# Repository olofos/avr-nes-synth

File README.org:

* NESSynth

  /NESSynth/ is an overcomplicated machine that plays NES music. /NESSynth/ currently supports four of the five channels present in the NES Audio Processing Unit (APU):
  - Two pulse, or square wave, channels
  - A triangle wave
  - A random noise channel

  There is currently no support for a DCM channel.

  /NESSynth/ has a menu system where the user can choose which game soundtrack is to be played.
  There is furthermore support for a playlist to which individual tracks can be added and played back.

** Hardware overview

  Each *channel* is processed separately by firmware running on an 8-bit ATMega88p microcontroller.
  An ATMega328p microcontroller acts as a central *controller*, reading track information from an SD card and writing the corresponding instructions to the channels.
  The controller is furthermore connected to an 128x64 pixel SSD1306 OLED display on which information about the current track, as well as a simple menu system, is displayed.
  User input is processed through an additional ATMega88p microcontroller which acts like an *io-bridge*, communicating with the main controller over I2C.
  The io-bridge is connected to four user buttons, four LEDs an a UART header for debugging.

  The following block diagram gives an overview of the architecture of /NESSynth/.

  #+HTML: 

*** 8-bit bus

   The controller communicates with the channels using an *8-bit parallel bus*.
   Writes to the bus are signalled on the *data clock* line.
   A rising clock signals that an address has been written on the bus, and a falling clock signals that a value that is to be written to the register at the previous address has been written on the bus.
   A new address or value is written every 33us, and the channels have to ensure that the data has been read from the bus within that time frame.

*** Frame clock

   In addition to the 8-bit bus, the controller provides the channel with a frame clock, which fires at a constant rate of 240 Hz.
   The frame clock is used to regularly update the output wave forms by applying the various effects such as the length counters and sweep units.

*** Channels

   Each channel emulates one of the channels on the NES APU.
   They react to writes to the corresponding registers appearing on the data bus and at each tick of the frame clock they clock the relevant output units in order to create effects such as sweep and envelope decay.

   The channels output sound at a frequency that is obtained by dividing the NTSC APU frequency of 1.789773 MHz by an integer, the /period/.
   The microcontrollers in the channels are clocked using a crystal with resonant frequency 14.3818 MHz, which is a multiple of the APU frequency.

   The PCBs of the channels have two jumpers, *CONF0* and *CONF1*, which can be used to configure which of the four APU channels the microcontroller is emulating.
   The possible settings are given in the following table.

   | CONF1      | CONF0      | Channel        |
   |------------+------------+----------------|
   | Fitted     | Fitted     | Square wave #1 |
   | Fitted     | Not fitted | Square wave #2 |
   | Not fitted | Fitted     | Triangle wave  |
   | Not fitted | Not fitted | Noise          |

   Each channel has a four bit R2R DAC that is used to construct the outgoing audio wave form.

   - Square wave channels

     The two square wave channels output a square wave with a duty cycle that can be set to 12.5%, 25%, 50% or 75%. The output volume of the square wave channels can be set to one of 16 levels, and can be modulated using the envelope decay unit. The square wave channels further support a sweep function to modulate the output frequency, as well as a length counter.

   - Triangle wave

     The triangle wave channel outputs a 32-step triangle wave of constant volume. For a given period, the frequency of the triangle wave is half of that of a square wave of the same period. The triangle wave channel supports a length counter and a linear counter which both can be used to limit the amount of time a note is played.

   - Noise channel

     The noise channel outputs noise that is generated using a linear feedback shift register. The feedback can be taken from two different taps of the shift registers. The volume of the noise channel can be configured to be constant, with 16 possible output levels, or can be varied over time using the envelope decay unit. The noise channel also supports a length counter.

*** Audio output

    The output of each channel is mixed together and then passed through a low pass filter with corner frequency 16 Hz and a high pass filter with corner frequency 16 kHz.
    The signal is the amplified using an LM386 audio amplifier before going to an 8 ohm speaker.

** Firmware

   The firmware for /NESSynth/ consists of three main pieces: the firmware for the main controller, the io-bridge and for the channels.
   The firmware is written using [[http://www.nongnu.org/avr-libc/user-manual/][avr-libc]] and compiled using avr-gcc.

   The controller has a menu system which is displayed on the OLED display.
   The menu system supports menus stored either on an SD card, in the flash memory of the controller, or in the EEPROM.
   It allows the user to play all the tracks from a particular game or to create a playlist with up to 128 tracks.
   The playlist is stored in the EEPROM of the controller.

   When playing a track, the controller reads the song data from the SD card where it is stored in a custom binary format (see below).
   The song data records the state of the APU registers at 60 Hz, and the controller outputs the data on the 8-bit bus.
   The song data is split into frames, and the controller plays the frames back at 60 Hz.

   The controller firmware includes a custom SD card and FAT32 drivers.
   The FAT32 driver does not read the FAT table into memory, which means that it has to search the table while reading data off the SD card.
   To improve performance when seeking in small files there is a cluster cache where the first few clusters in the currently open file.

   The firmware of the channels simply listens to writes to the registers relevant to the corresponding APU channel and puts out a wave form on the DAC.
   The channel firmware is heavily interrupt based.
   In order to improve the performance of the main timer interrupt, which is responsible for actually constructing the audio out signal, the interrupt handler has been written in assembly code.
   For clarity there is also a C version of the interrupt handler, which can be enabled by removing the ASMINTERRUPT flag in the Makefile of the channel firmware source code.

*** Song file format

   The binary file format is very simple.
   It consists of a number of two-byte records, with the first byte indicating an address, and the second byte the corresponding values.
   There are three special records

   | Address | Value | Meaning      |
   |---------+-------+--------------|
   |    0xF1 |  0xF1 | End of frame |
   |    0xFF |  0xFF | End of file  |
   |    0xFE |  0xFE | Loop         |

   The loop record is followed by a 16-bit byte address indicating which byte in the file to loop back to.

   In order to construct a data file from an NSF files, a player based on a custom version of the [[http://www.slack.net/~ant/libs/audio.html#Game_Music_Emu][Game_Music_Emu 0.5.2]] library is used.
   The custom NSF player outputs data in a text file.
   This data is then processed through a couple of simple programs which are used to detect loops in the track, and to convert the data into the binary file format described above.

** Acknowledgements

   The [[https://wiki.nesdev.com/w/index.php/APU][APU pages]] of the [[https://wiki.nesdev.com/][NesDev wiki]] have been invaluable for providing information about the inner workings of the NES APU, as has the [[http://nesdev.com/NESSOUND.txt][NESSOUND]] document by Brad Taylor.

   The NSF player that is used to create binary sound data files is based on the  [[http://www.slack.net/~ant/libs/audio.html#Game_Music_Emu][Game_Music_Emu 0.5.2]] library by Shay Green, which is licensed under the [[https://www.gnu.org/licenses/old-licenses/lgpl-2.1.en.html][GNU Lesser General Public License, Version 2.1]].

   The circular buffer implementation in lib/cbuf.h is inspired by the one in [[https://github.com/dhylands/TimerUART][TimerUART]].

   For 3d rendering of the boards, 3d models from [[https://github.com/ab2tech/KiCad][ab2tech]], which are licensed under [[http://creativecommons.org/licenses/by-nc-sa/3.0/deed.en_US][Creative Commons Attribution-NonCommercial-ShareAlike 3.0 Unported License]], and from [[https://github.com/JorgeAparicio/libKiCad][libKiCad]], which are licensed under [[hardware/lib/3d_models/walter/license.txt][Creative Commons license v3.0, Attribution-Share Alike]], have been used.

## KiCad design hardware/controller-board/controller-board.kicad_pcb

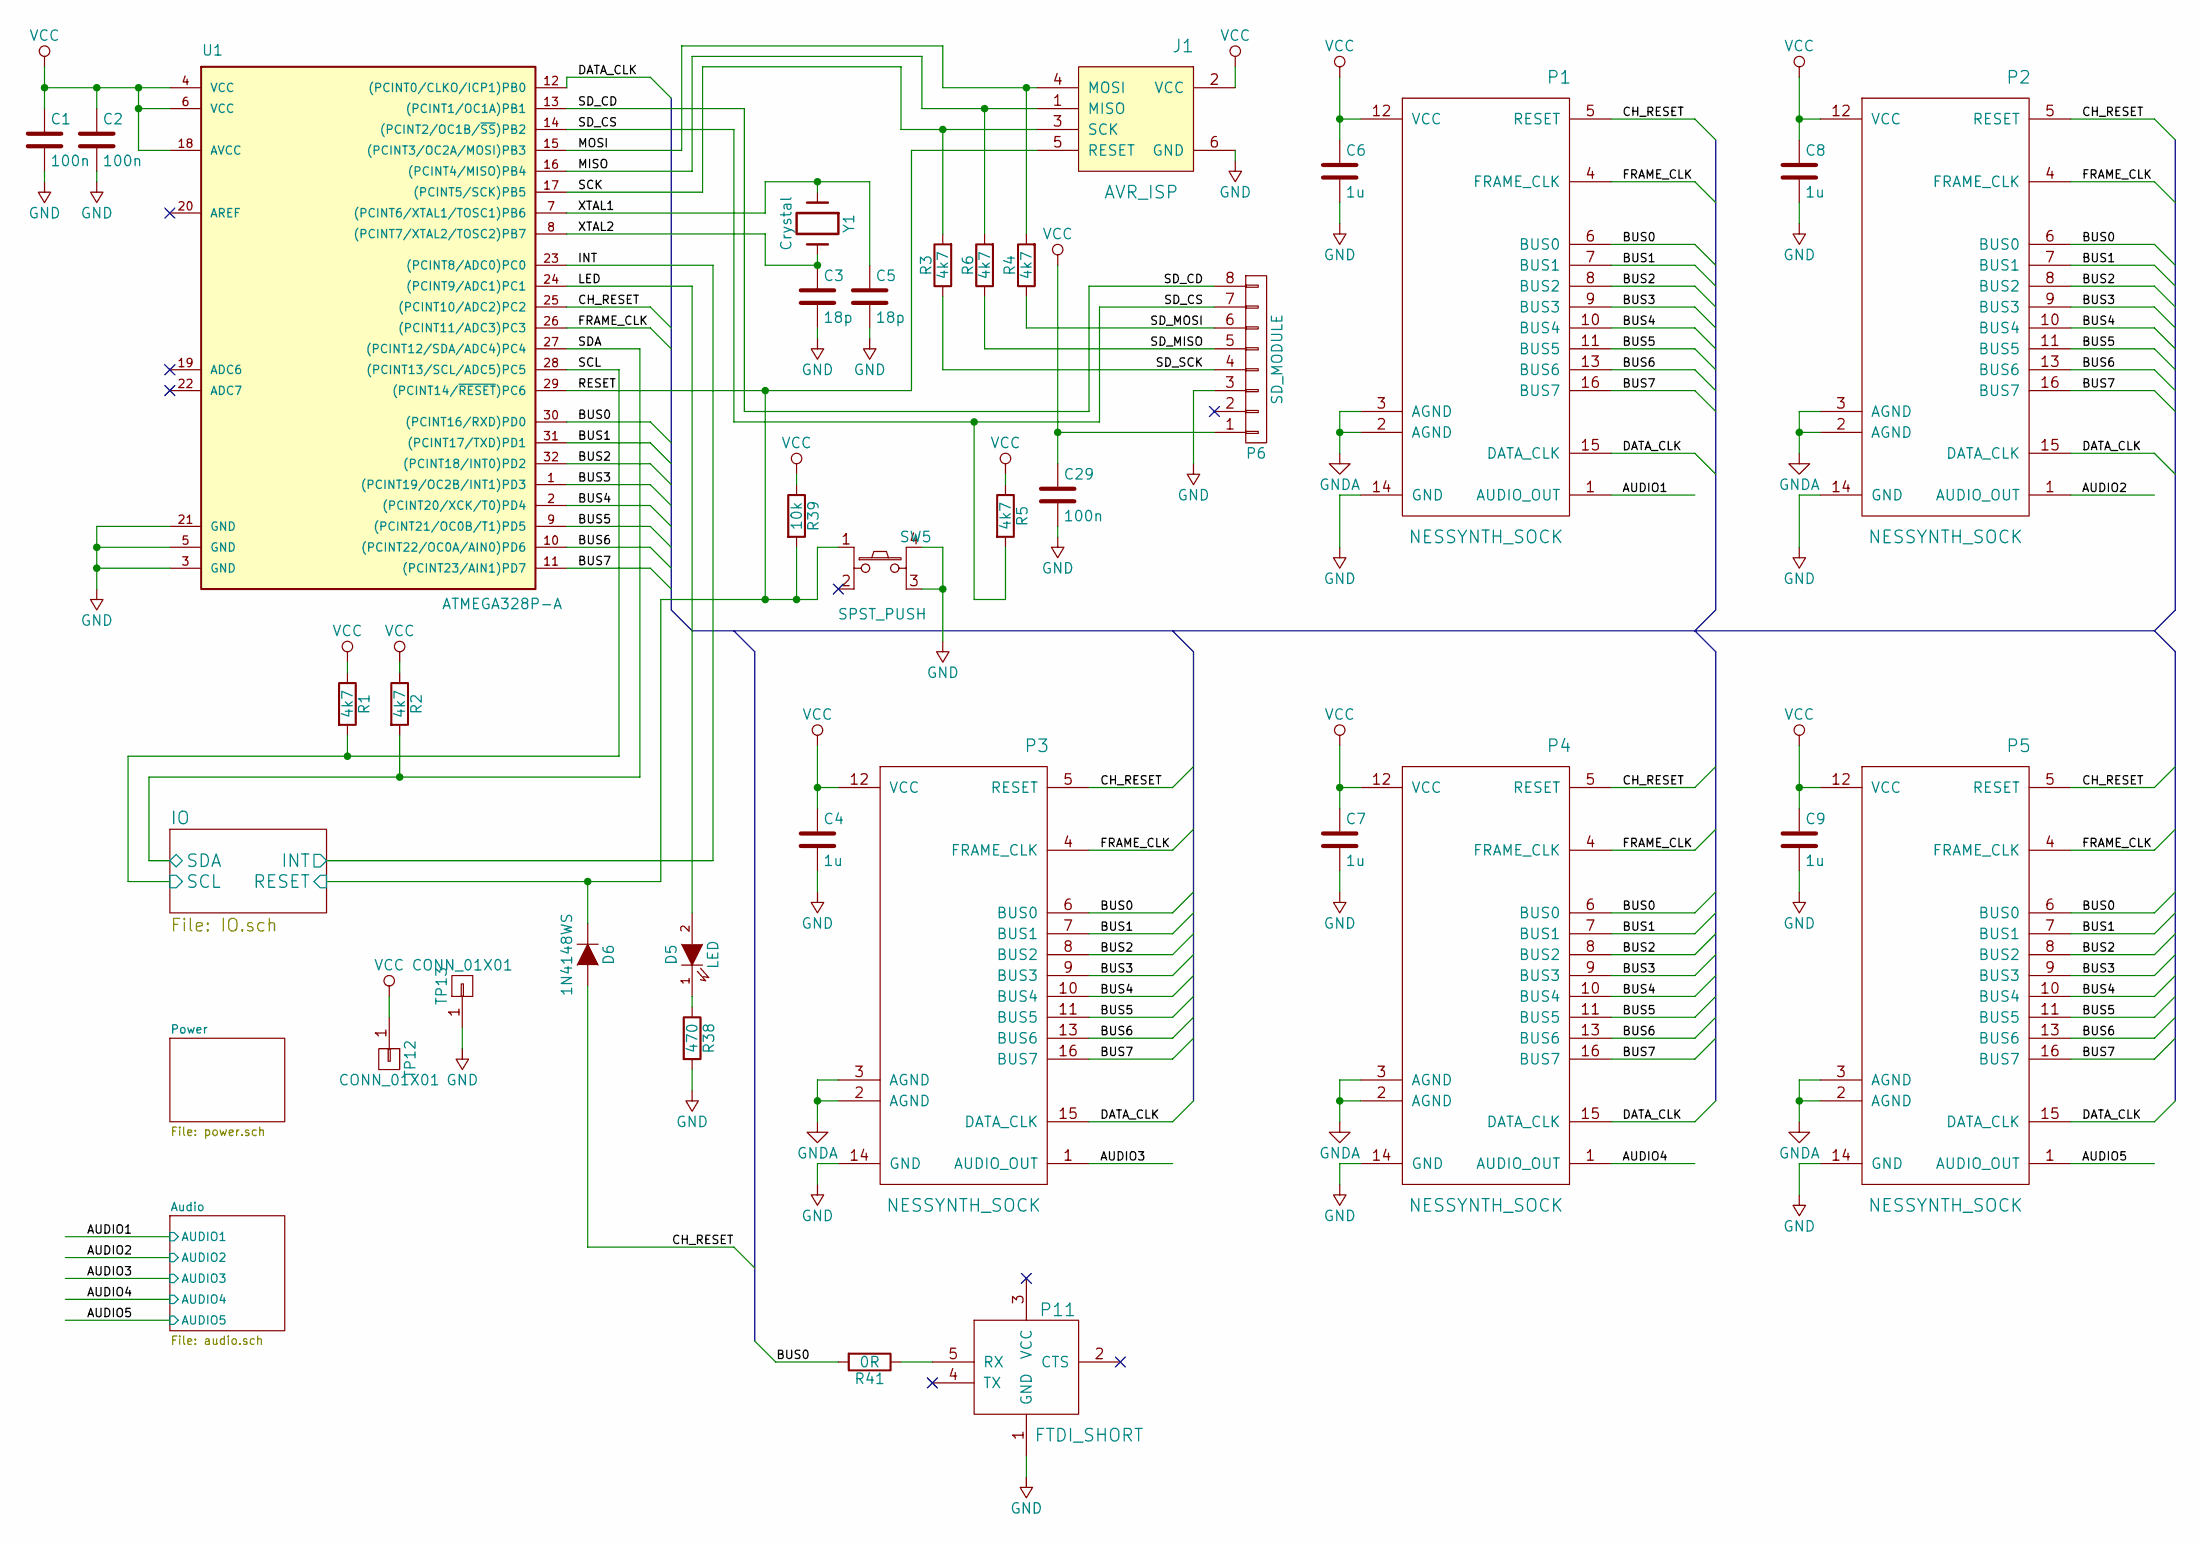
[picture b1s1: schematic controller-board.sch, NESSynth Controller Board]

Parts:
C1, C2, C29: 100n; C_0805_HandSoldering
C3, C5: 18p; C_0805_HandSoldering
C4, C6, C7, C8, C9: 1u; C_0805_HandSoldering
D5: LED; LED_0805
D6: 1N4148WS; SOD-323
J1: AVR_ISP; AVR_ISP_SMALL
P1, P2, P3, P4, P5: NESSYNTH_SOCK; Socket_Strip_Straight_2x08
P6: SD_MODULE; Socket_Strip_Straight_1x08
P11: FTDI_SHORT; Pin_Header_Straight_1x05
R1, R2, R3, R4, R5, R6: 4k7; R_0805_HandSoldering
R38: 470; R_0805_HandSoldering
R39: 10k; R_0805_HandSoldering
R41: 0R; R_0805_HandSoldering
SW5: SPST_PUSH; SW_PUSH_SMALL_4
TP12: CONN_01X01; Measurement_Point_Round-SMD-Pad_Small
TP13: CONN_01X01; Measurement_Point_Square-SMD-Pad_Small
U1: ATMEGA328P-A; TQFP-32_7x7mm_Pitch0.8mm
Y1: Crystal; Crystal_HC49-U_Vertical

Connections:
/Audio/AUDIO1: P1.1 (AUDIO_OUT); also elsewhere on the board
/Audio/AUDIO2: P2.1 (AUDIO_OUT); also elsewhere on the board
/Audio/AUDIO3: P3.1 (AUDIO_OUT); also elsewhere on the board
/Audio/AUDIO4: P4.1 (AUDIO_OUT); also elsewhere on the board
/Audio/AUDIO5: P5.1 (AUDIO_OUT); also elsewhere on the board
/BUS0: P1.6 (BUS0), P2.6 (BUS0), P3.6 (BUS0), P4.6 (BUS0), P5.6 (BUS0), R41.2, U1.30 ((PCINT16/RXD)PD0)
/BUS1: P1.7 (BUS1), P2.7 (BUS1), P3.7 (BUS1), P4.7 (BUS1), P5.7 (BUS1), U1.31 ((PCINT17/TXD)PD1)
/BUS2: P1.8 (BUS2), P2.8 (BUS2), P3.8 (BUS2), P4.8 (BUS2), P5.8 (BUS2), U1.32 ((PCINT18/INT0)PD2)
/BUS3: P1.9 (BUS3), P2.9 (BUS3), P3.9 (BUS3), P4.9 (BUS3), P5.9 (BUS3), U1.1 ((PCINT19/OC2B/INT1)PD3)
/BUS4: P1.10 (BUS4), P2.10 (BUS4), P3.10 (BUS4), P4.10 (BUS4), P5.10 (BUS4), U1.2 ((PCINT20/XCK/T0)PD4)
/BUS5: P1.11 (BUS5), P2.11 (BUS5), P3.11 (BUS5), P4.11 (BUS5), P5.11 (BUS5), U1.9 ((PCINT21/OC0B/T1)PD5)
/BUS6: P1.13 (BUS6), P2.13 (BUS6), P3.13 (BUS6), P4.13 (BUS6), P5.13 (BUS6), U1.10 ((PCINT22/OC0A/AIN0)PD6)
/BUS7: P1.16 (BUS7), P2.16 (BUS7), P3.16 (BUS7), P4.16 (BUS7), P5.16 (BUS7), U1.11 ((PCINT23/AIN1)PD7)
/CH_RESET: D6.2 (A), P1.5 (RESET), P2.5 (RESET), P3.5 (RESET), P4.5 (RESET), P5.5 (RESET), U1.25 ((PCINT10/ADC2)PC2)
/DATA_CLK: P1.15 (DATA_CLK), P2.15 (DATA_CLK), P3.15 (DATA_CLK), P4.15 (DATA_CLK), P5.15 (DATA_CLK), U1.12 ((PCINT0/CLKO/ICP1)PB0)
/FRAME_CLK: P1.4 (FRAME_CLK), P2.4 (FRAME_CLK), P3.4 (FRAME_CLK), P4.4 (FRAME_CLK), P5.4 (FRAME_CLK), U1.26 ((PCINT11/ADC3)PC3)
/IO/INT: U1.23 ((PCINT8/ADC0)PC0); also elsewhere on the board
/IO/RESET: D6.1 (K), J1.5 (RESET), R39.2, SW5.1 (A1), U1.29 ((PCINT14/~RESET~)PC6); also elsewhere on the board
/IO/SCL: R1.2, U1.28 ((PCINT13/SCL/ADC5)PC5); also elsewhere on the board
/IO/SDA: R2.2, U1.27 ((PCINT12/SDA/ADC4)PC4); also elsewhere on the board
/LED: D5.2 (A), U1.24 ((PCINT9/ADC1)PC1)
/MISO: J1.1 (MISO), R6.2, U1.16 ((PCINT4/MISO)PB4)
/MOSI: J1.4 (MOSI), R4.2, U1.15 ((PCINT3/OC2A/MOSI)PB3)
/SCK: J1.3 (SCK), R3.2, U1.17 ((PCINT5/SCK)PB5)
/SD_CD: P6.8, U1.13 ((PCINT1/OC1A)PB1)
/SD_CS: P6.7, R5.2, U1.14 ((PCINT2/OC1B/~SS~)PB2)
/SD_MISO: P6.5, R6.1
/SD_MOSI: P6.6, R4.1
/SD_SCK: P6.4, R3.1
/XTAL1: C5.1, U1.7 ((PCINT6/XTAL1/TOSC1)PB6), Y1.1
/XTAL2: C3.1, U1.8 ((PCINT7/XTAL2/TOSC2)PB7), Y1.2
GND: C1.2, C2.2, C3.2, C4.2, C5.2, C6.2, C7.2, C8.2, C9.2, C29.2, J1.6 (GND), P1.2 (AGND), P1.3 (AGND), P1.14 (GND), P2.2 (AGND), P2.3 (AGND), P2.14 (GND), P3.2 (AGND), P3.3 (AGND), P3.14 (GND), P4.2 (AGND), P4.3 (AGND), P4.14 (GND), P5.2 (AGND), P5.3 (AGND), P5.14 (GND), P6.3, P11.1 (GND), R38.2, SW5.3 (B2), SW5.4 (B1), TP13.1, U1.3 (GND), U1.5 (GND), U1.21 (GND); also elsewhere on the board
unnamed: D5.1 (K), R38.1
unnamed: P11.5 (RX), R41.1
VCC: C1.1, C2.1, C4.1, C6.1, C7.1, C8.1, C9.1, C29.1, J1.2 (VCC), P1.12 (VCC), P2.12 (VCC), P3.12 (VCC), P4.12 (VCC), P5.12 (VCC), P6.1, R1.1, R2.1, R5.1, R39.1, TP12.1, U1.4 (VCC), U1.6 (VCC), U1.18 (AVCC); also elsewhere on the board

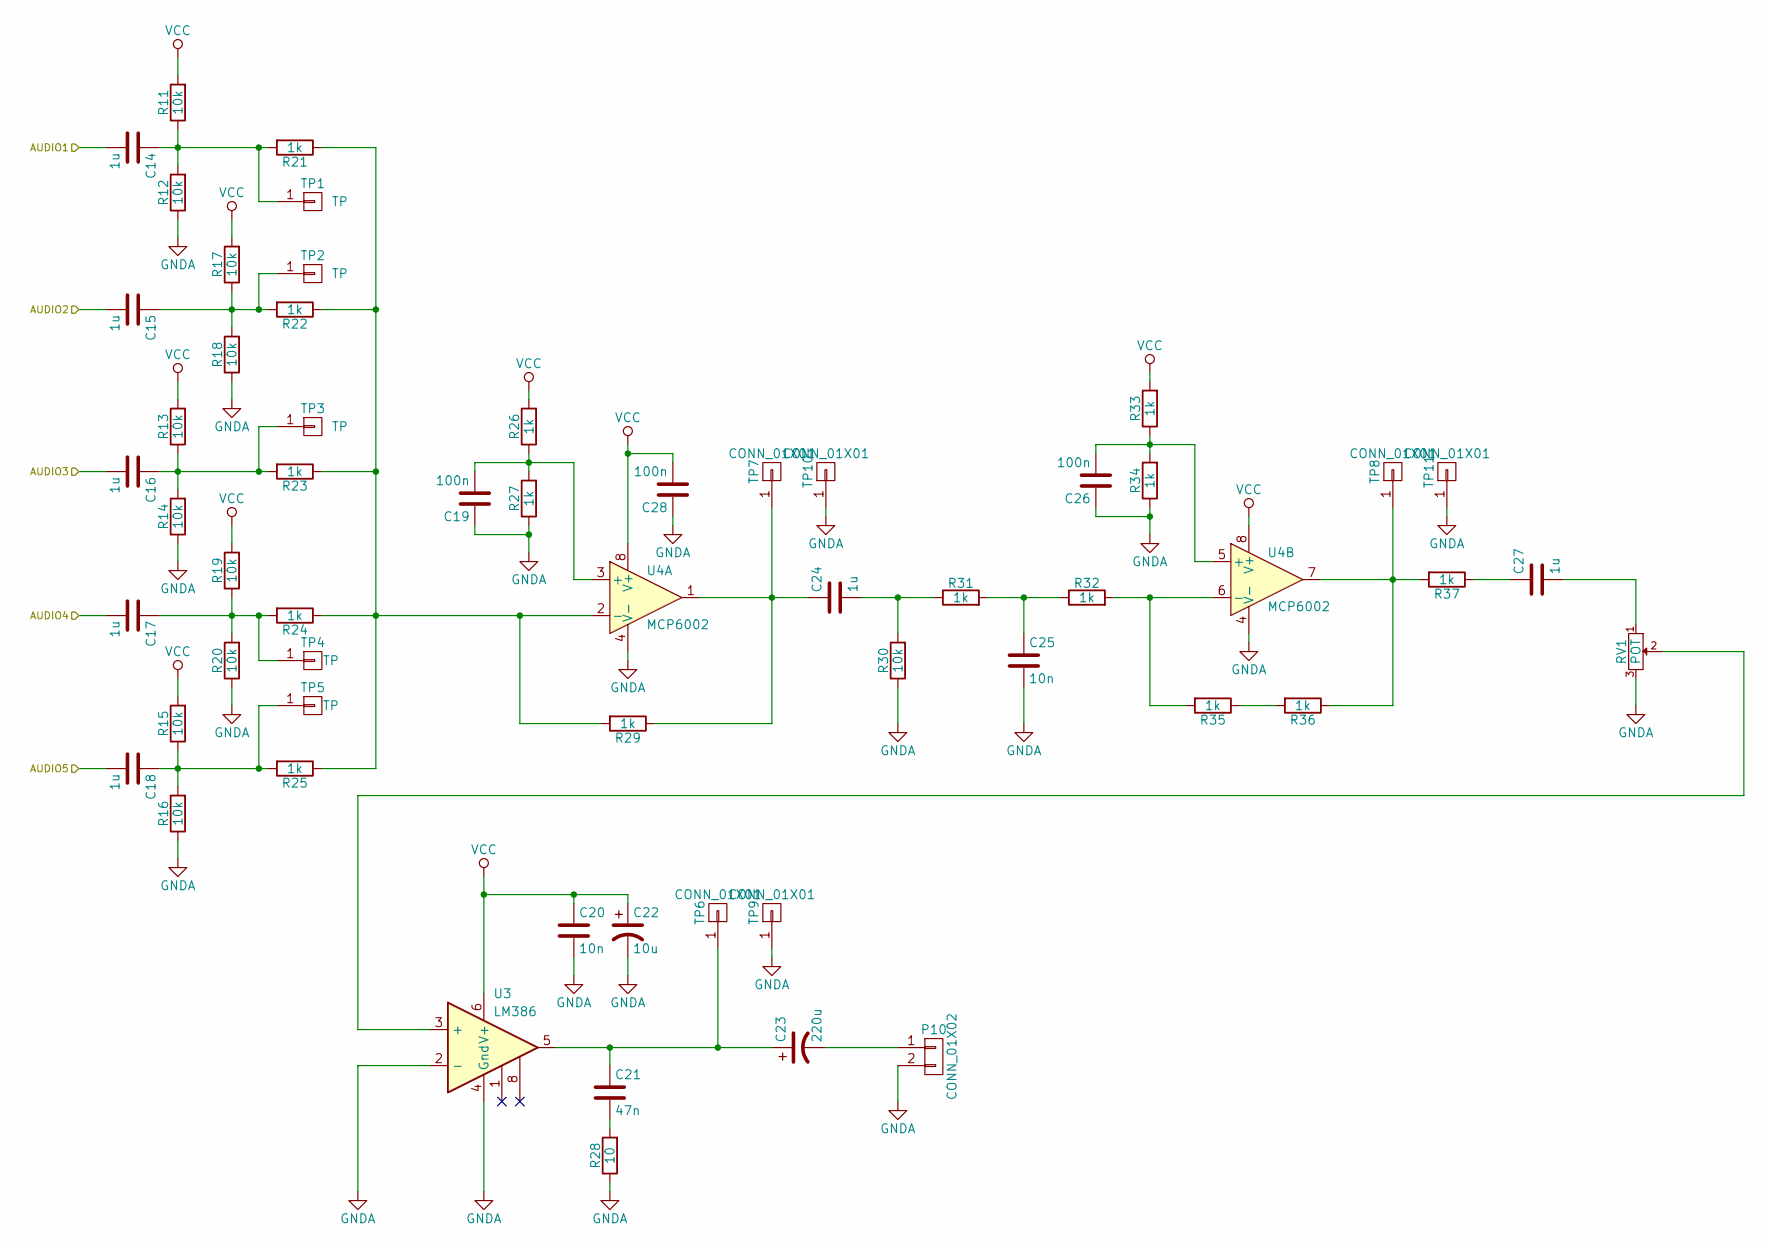
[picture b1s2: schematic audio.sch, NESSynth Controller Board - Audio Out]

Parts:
C14, C15, C16, C17, C18, C24, C27: 1u; C_0805_HandSoldering
C19, C26, C28: 100n; C_0805_HandSoldering
C20, C25: 10n; C_0805_HandSoldering
C21: 47n; C_0805_HandSoldering
C22: 10u; c_elec_6.3x5.7
C23: 220u; c_elec_6.3x5.7
P10: CONN_01X02; TerminalBlock_Pheonix_MPT-2.54mm_2pol
R11, R12, R13, R14, R15, R16, R17, R18, R19, R20, R30: 10k; R_0805_HandSoldering
R21, R22, R23, R24, R25, R26, R27, R29, R31, R32, R33, R34, R35, R36, R37: 1k; R_0805_HandSoldering
R28: 10; R_0805_HandSoldering
RV1: POT; Potentiometer_Alps-RK16-single_largePads
TP1, TP2, TP3, TP4, TP5: TP; TEST_POINT_THD
TP6, TP7, TP8: CONN_01X01; Measurement_Point_Round-SMD-Pad_Small
TP9, TP10, TP11: CONN_01X01; Measurement_Point_Square-SMD-Pad_Small
U3: LM386; SOIC-8_3.9x4.9mm_Pitch1.27mm
U4: MCP6002; SOIC-8_3.9x4.9mm_Pitch1.27mm

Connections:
/Audio/AUDIO1: C14.2; also elsewhere on the board
/Audio/AUDIO2: C15.2; also elsewhere on the board
/Audio/AUDIO3: C16.2; also elsewhere on the board
/Audio/AUDIO4: C17.2; also elsewhere on the board
/Audio/AUDIO5: C18.2; also elsewhere on the board
GND: C19.1, C20.2, C22.2, C25.2, C26.1, C28.1, P10.2, R12.1, R14.1, R16.1, R18.1, R20.1, R27.1, R28.1, R30.1, R34.1, RV1.3, TP9.1, TP10.1, TP11.1, U3.2 (-), U3.4 (Gnd), U4.4 (V-); also elsewhere on the board
unnamed: C14.1, R11.1, R12.2, R21.2, TP1.1
unnamed: C15.1, R17.1, R18.2, R22.2, TP2.1
unnamed: C16.1, R13.1, R14.2, R23.2, TP3.1
unnamed: C17.1, R19.1, R20.2, R24.2, TP4.1
unnamed: C18.1, R15.1, R16.2, R25.2, TP5.1
unnamed: C19.2, R26.1, R27.2, U4.3 (+)
unnamed: C21.1, C23.1, TP6.1, U3.5
unnamed: C21.2, R28.2
unnamed: C23.2, P10.1
unnamed: C24.1, R29.1, TP7.1, U4.1
unnamed: C24.2, R30.2, R31.1
unnamed: C25.1, R31.2, R32.1
unnamed: C26.2, R33.1, R34.2, U4.5 (+)
unnamed: C27.1, R37.1
unnamed: C27.2, RV1.1
unnamed: R21.1, R22.1, R23.1, R24.1, R25.1, R29.2, U4.2 (-)
unnamed: R32.2, R35.2, U4.6 (-)
unnamed: R35.1, R36.2
unnamed: R36.1, R37.2, TP8.1, U4.7
unnamed: RV1.2, U3.3 (+)
VCC: C20.1, C22.1, C28.2, R11.2, R13.2, R15.2, R17.2, R19.2, R26.2, R33.2, U3.6 (V+), U4.8 (V+); also elsewhere on the board

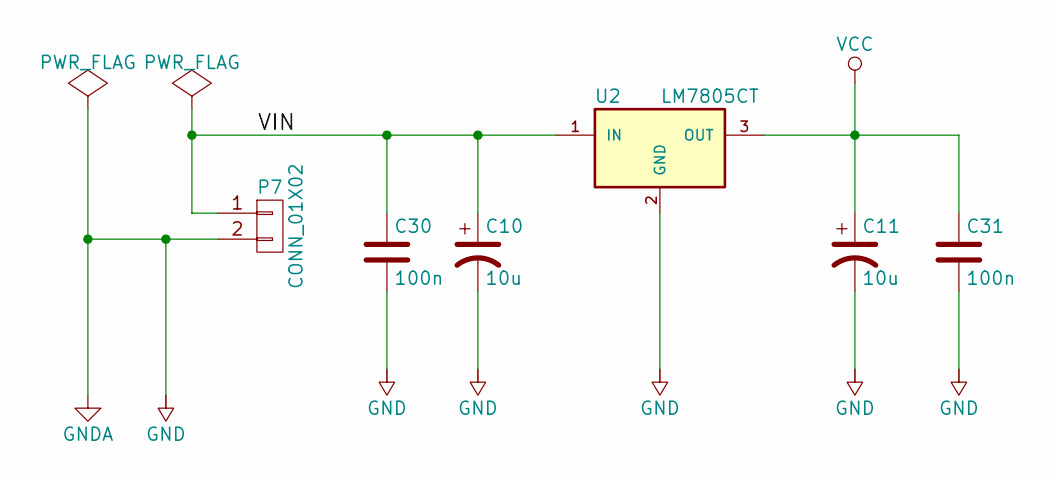
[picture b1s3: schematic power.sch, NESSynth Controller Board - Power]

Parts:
C10, C11: 10u; c_elec_6.3x5.7
C30, C31: 100n; C_0805_HandSoldering
P7: CONN_01X02; Pin_Header_Straight_1x02
U2: LM7805CT; TO-220_Neutral123_Vertical

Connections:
/Power/VIN: C10.1, C30.1, P7.1, U2.1 (IN)
GND: C10.2, C11.2, C30.2, C31.2, P7.2, U2.2 (GND); also elsewhere on the board
VCC: C11.1, C31.1, U2.3 (OUT); also elsewhere on the board

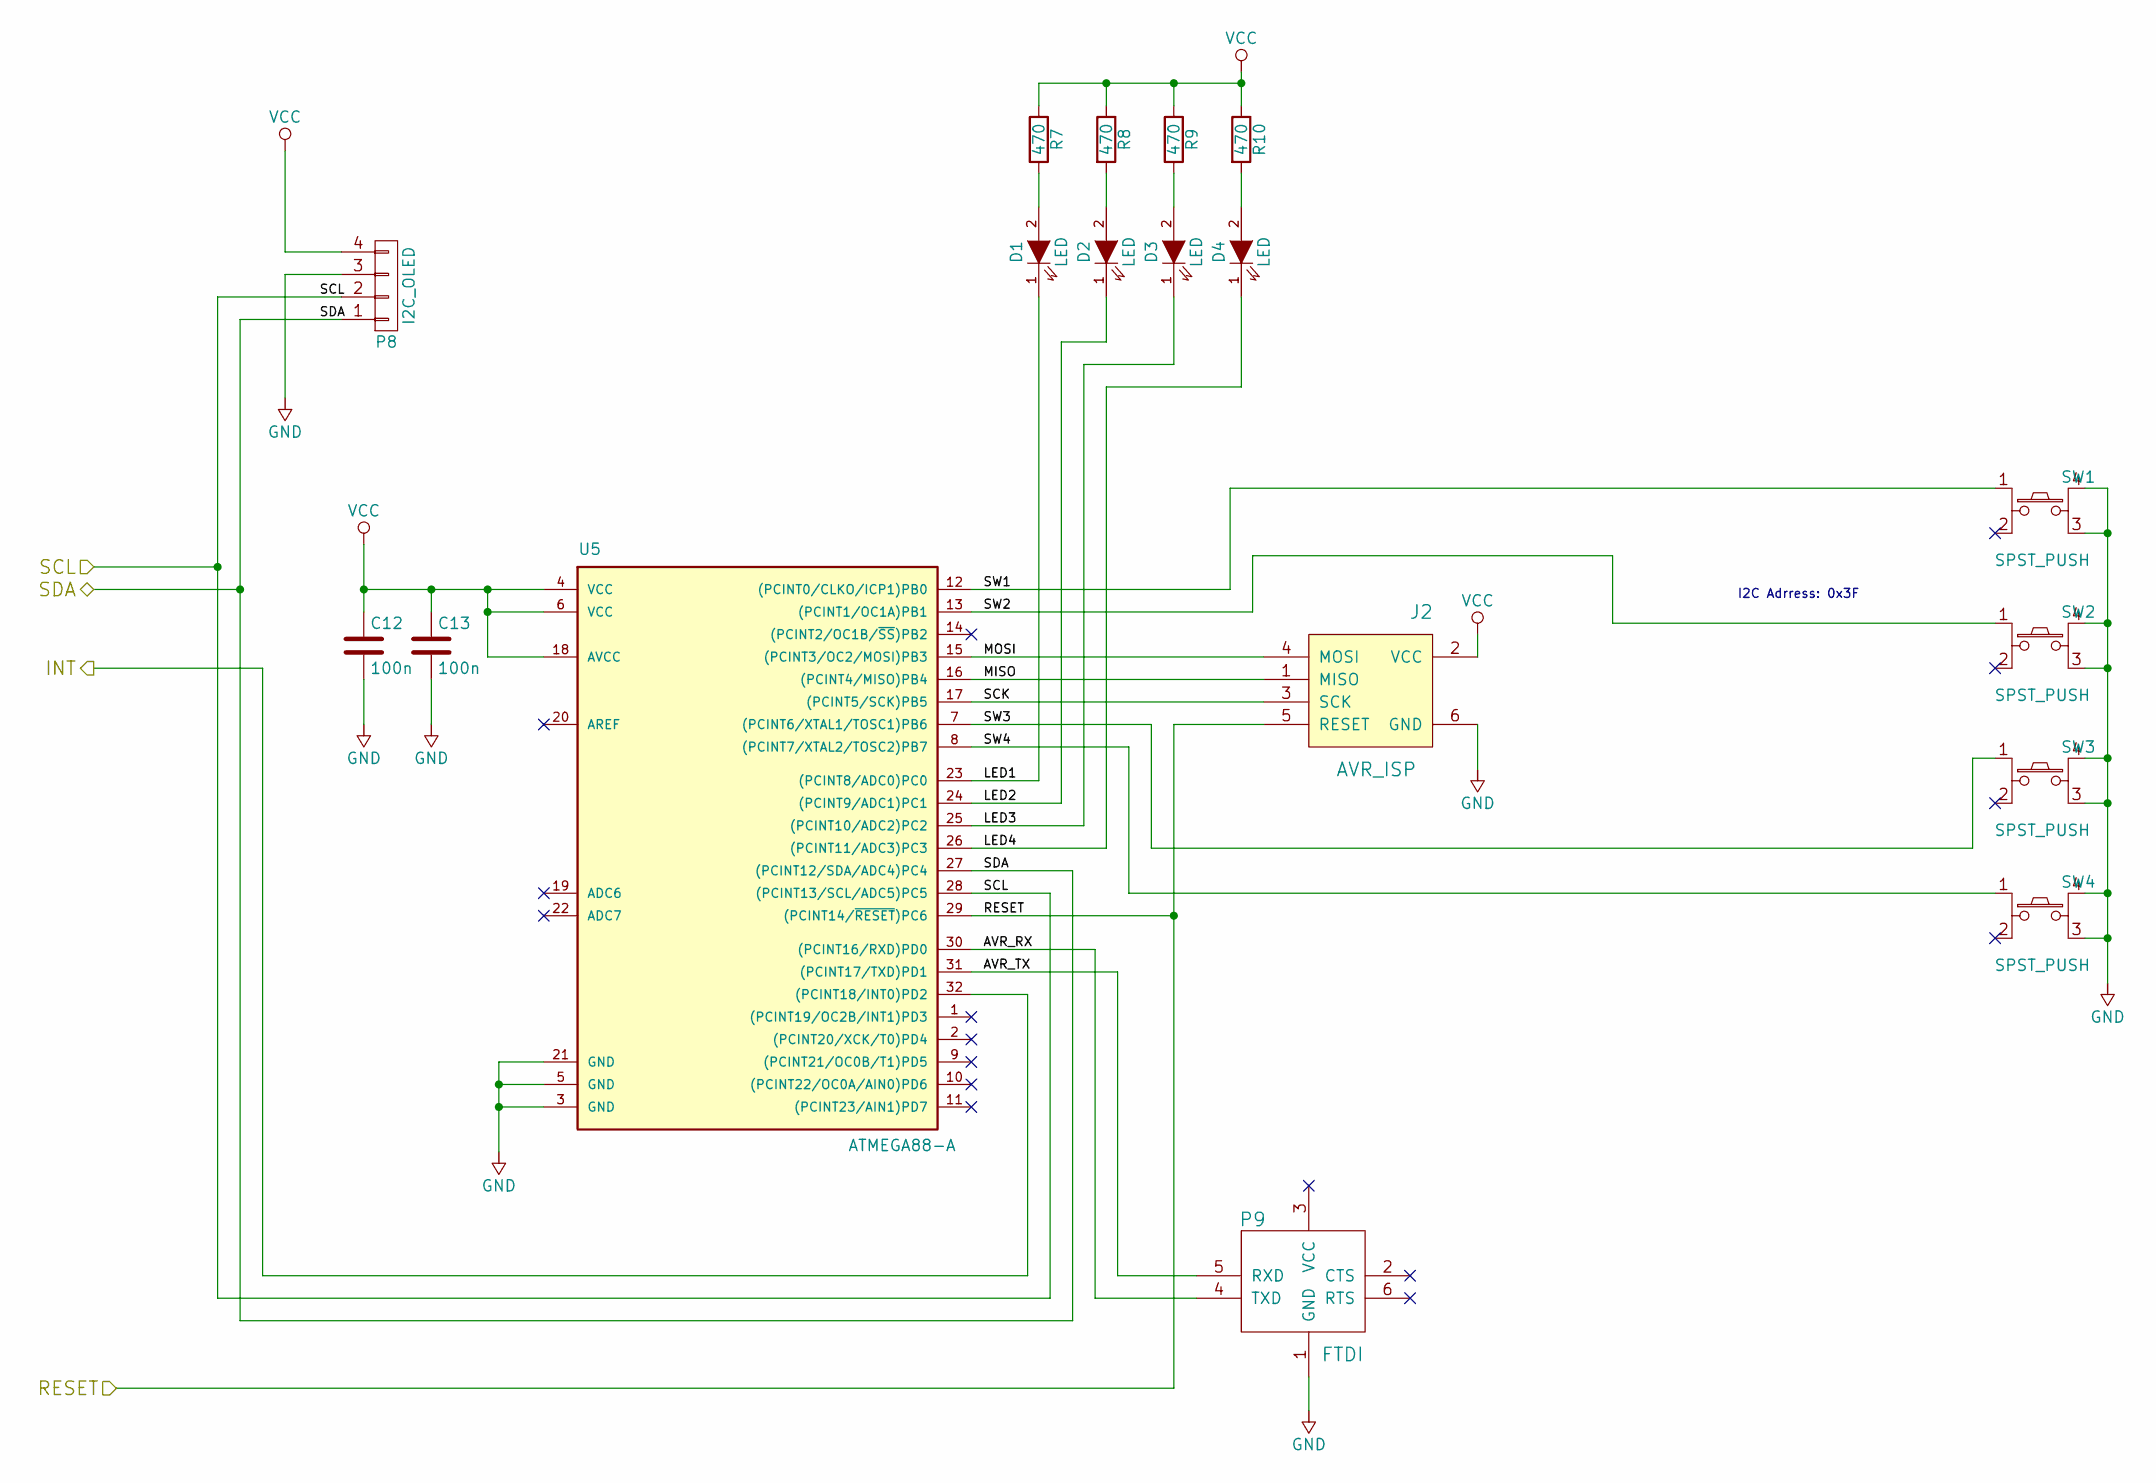
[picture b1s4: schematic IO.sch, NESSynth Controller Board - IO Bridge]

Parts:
C12, C13: 100n; C_0805_HandSoldering
D1, D2, D3, D4: LED; LED_0805
J2: AVR_ISP; AVR_ISP_SMALL
P8: I2C_OLED; LCD_I2C_96
P9: FTDI; Pin_Header_Straight_1x06
R7, R8, R9, R10: 470; R_0805_HandSoldering
SW1, SW2, SW3, SW4: SPST_PUSH; SW_PUSH_SMALL_4
U5: ATMEGA88-A; TQFP-32_7x7mm_Pitch0.8mm

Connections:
/IO/AVR_RX: P9.4 (TXD), U5.30 ((PCINT16/RXD)PD0)
/IO/AVR_TX: P9.5 (RXD), U5.31 ((PCINT17/TXD)PD1)
/IO/INT: U5.32 ((PCINT18/INT0)PD2); also elsewhere on the board
/IO/LED1: D1.1 (K), U5.23 ((PCINT8/ADC0)PC0)
/IO/LED2: D2.1 (K), U5.24 ((PCINT9/ADC1)PC1)
/IO/LED3: D3.1 (K), U5.25 ((PCINT10/ADC2)PC2)
/IO/LED4: D4.1 (K), U5.26 ((PCINT11/ADC3)PC3)
/IO/MISO: J2.1 (MISO), U5.16 ((PCINT4/MISO)PB4)
/IO/MOSI: J2.4 (MOSI), U5.15 ((PCINT3/OC2/MOSI)PB3)
/IO/RESET: J2.5 (RESET), U5.29 ((PCINT14/~RESET~)PC6); also elsewhere on the board
/IO/SCK: J2.3 (SCK), U5.17 ((PCINT5/SCK)PB5)
/IO/SCL: P8.2, U5.28 ((PCINT13/SCL/ADC5)PC5); also elsewhere on the board
/IO/SDA: P8.1, U5.27 ((PCINT12/SDA/ADC4)PC4); also elsewhere on the board
/IO/SW1: SW1.1 (A1), U5.12 ((PCINT0/CLKO/ICP1)PB0)
/IO/SW2: SW2.1 (A1), U5.13 ((PCINT1/OC1A)PB1)
/IO/SW3: SW3.1 (A1), U5.7 ((PCINT6/XTAL1/TOSC1)PB6)
/IO/SW4: SW4.1 (A1), U5.8 ((PCINT7/XTAL2/TOSC2)PB7)
GND: C12.2, C13.2, J2.6 (GND), P8.3, P9.1 (GND), SW1.3 (B2), SW1.4 (B1), SW2.3 (B2), SW2.4 (B1), SW3.3 (B2), SW3.4 (B1), SW4.3 (B2), SW4.4 (B1), U5.3 (GND), U5.5 (GND), U5.21 (GND); also elsewhere on the board
unnamed: D1.2 (A), R7.2
unnamed: D2.2 (A), R8.2
unnamed: D3.2 (A), R9.2
unnamed: D4.2 (A), R10.2
VCC: C12.1, C13.1, J2.2 (VCC), P8.4, R7.1, R8.1, R9.1, R10.1, U5.4 (VCC), U5.6 (VCC), U5.18 (AVCC); also elsewhere on the board

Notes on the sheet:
I2C Adrress: 0x3F

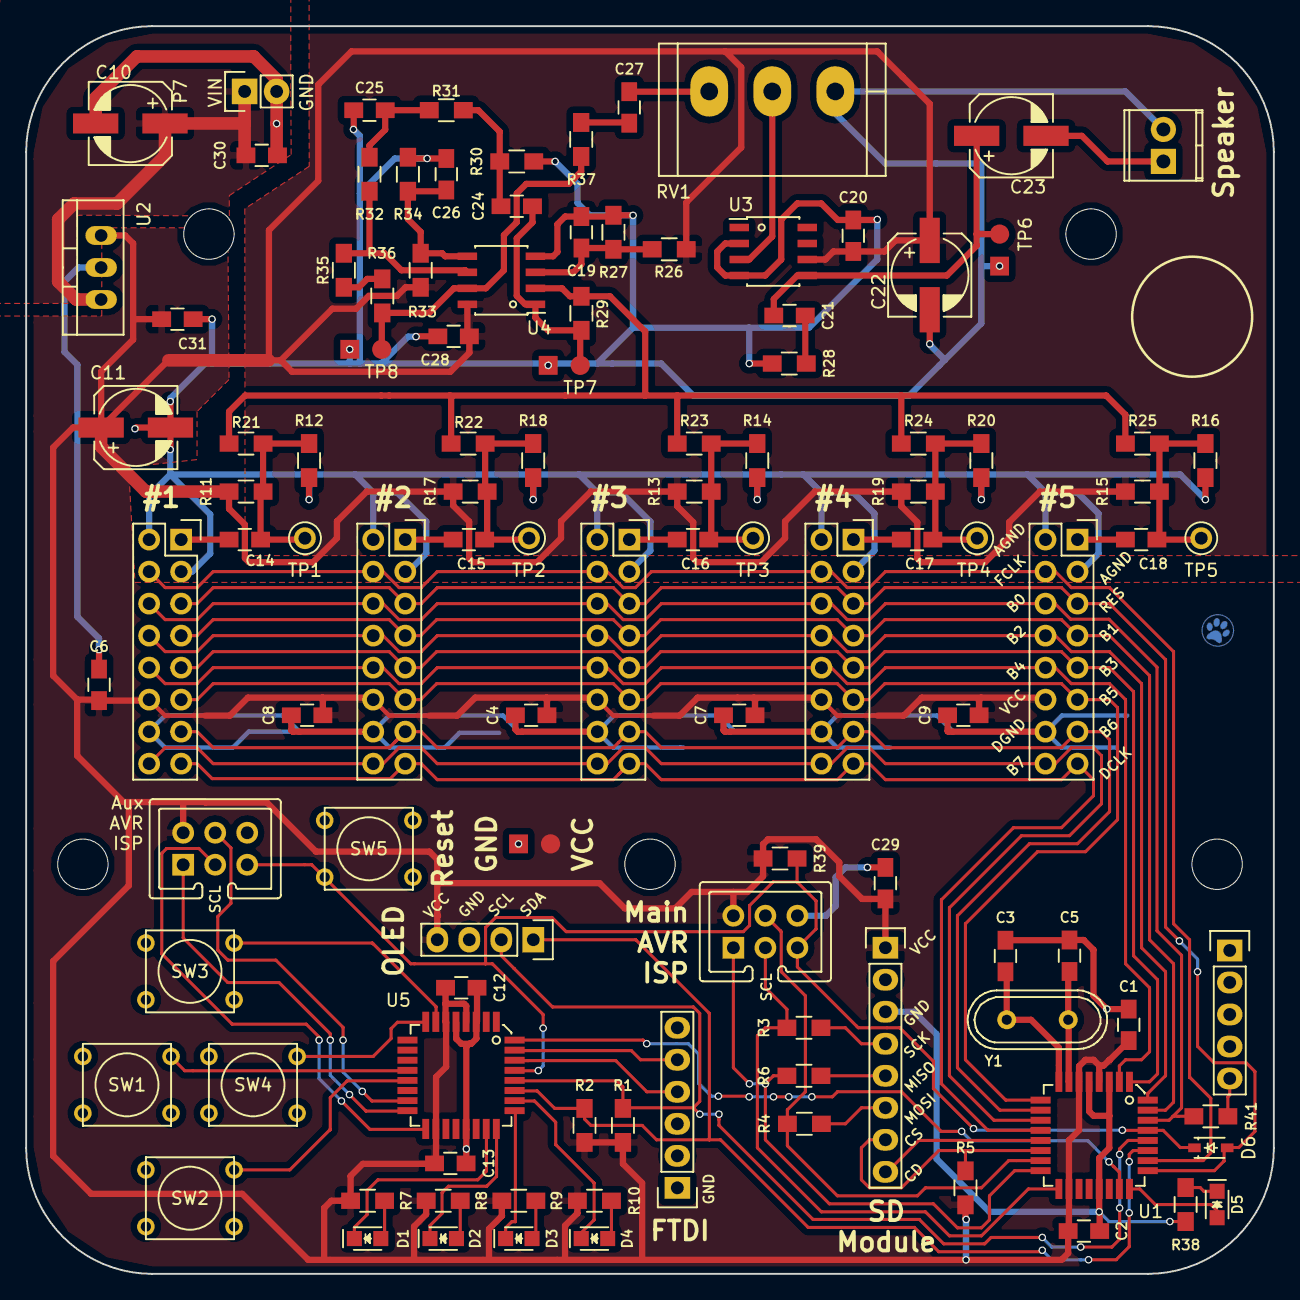
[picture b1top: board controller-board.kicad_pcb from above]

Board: 2 copper layers, 99.0 x 99.0 mm, 120 parts (0 on the bottom side), 73 nets.

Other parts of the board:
MH1, MH2, MH3, MH4, MH5: MOUNTING_HOLE; MountingHole_4mm

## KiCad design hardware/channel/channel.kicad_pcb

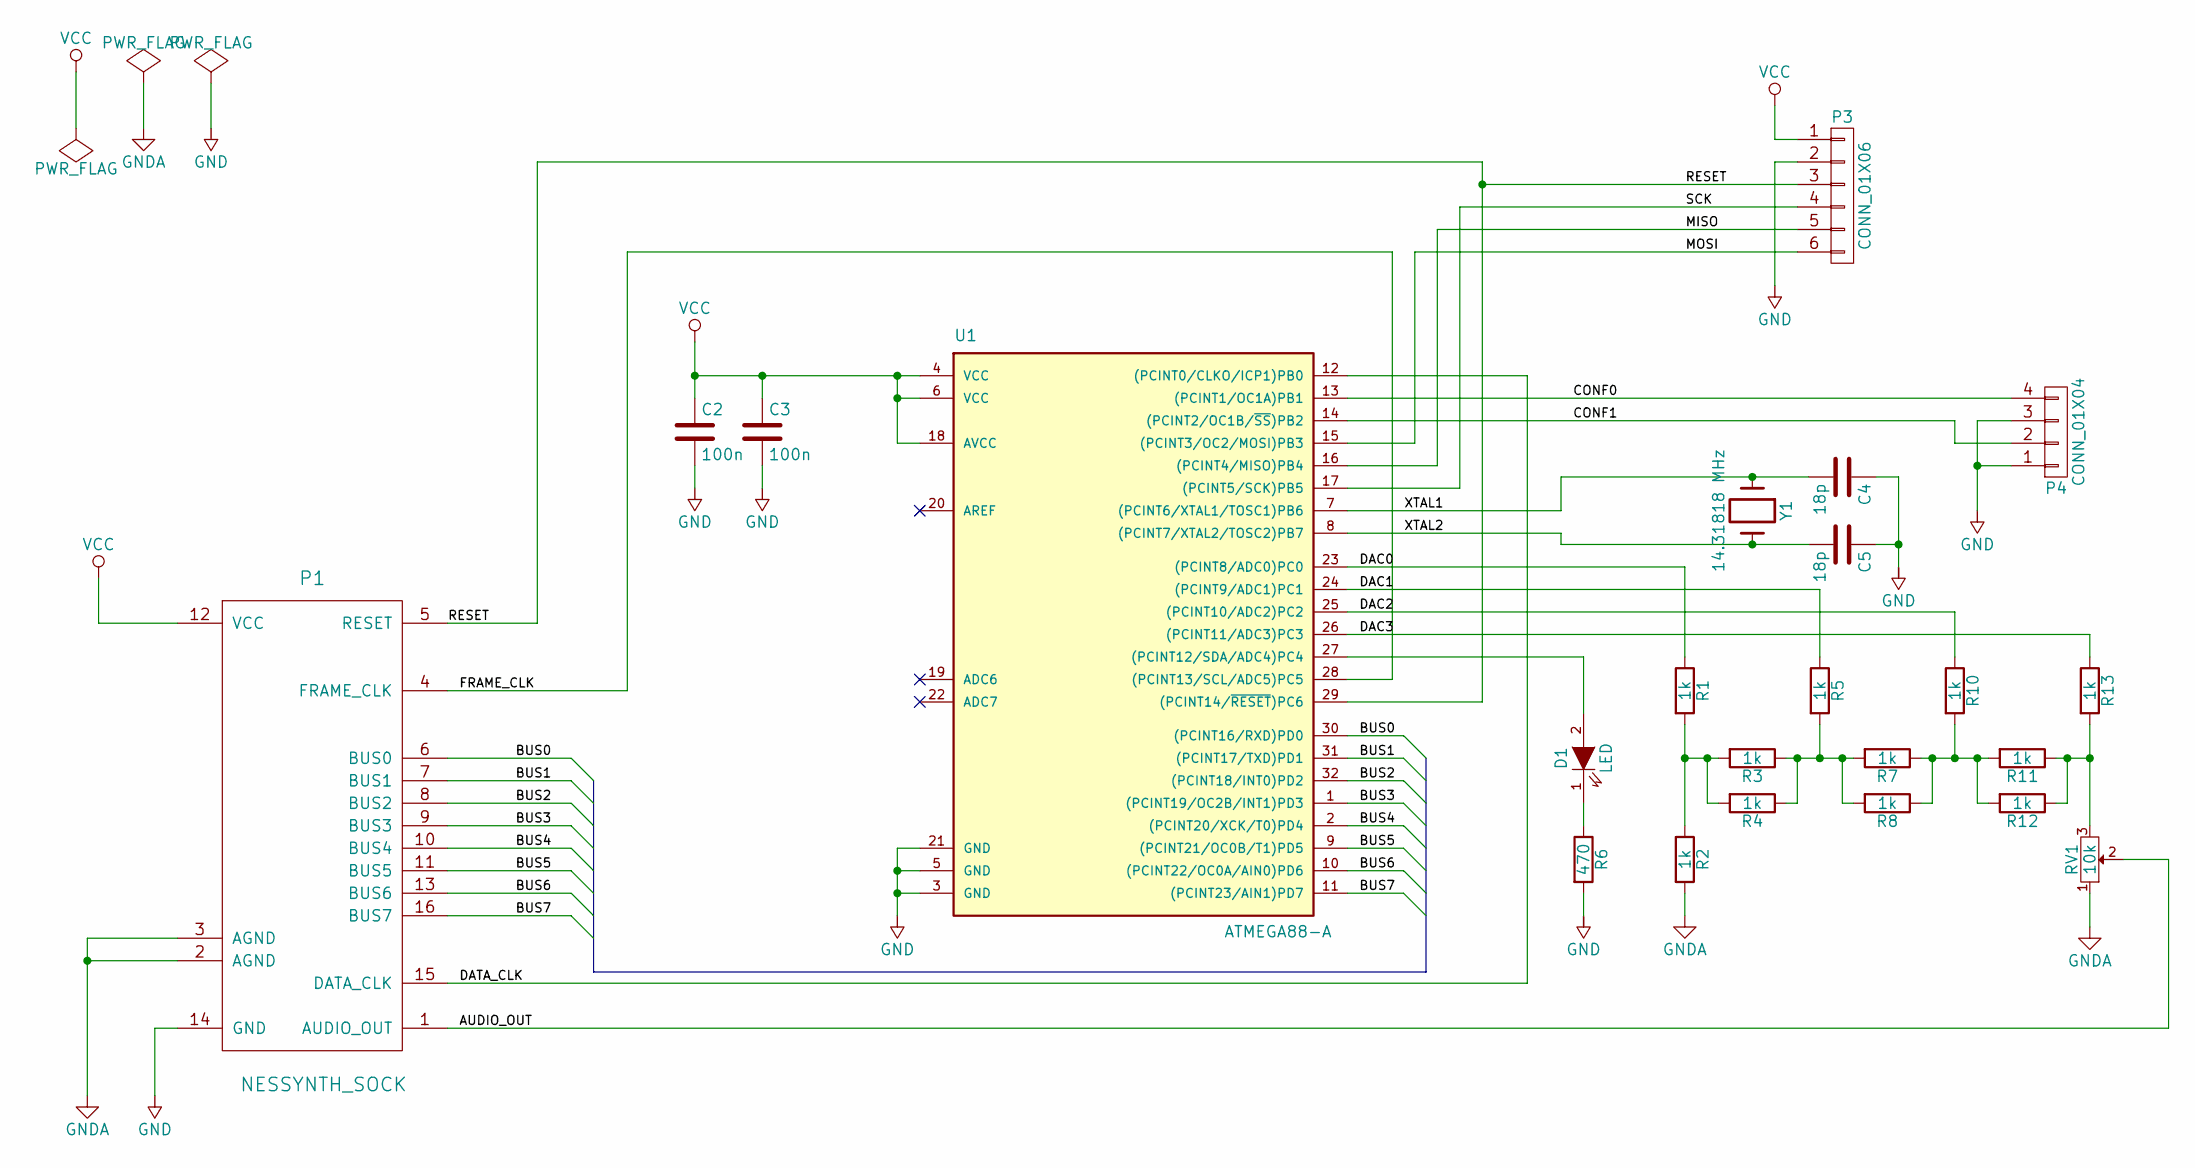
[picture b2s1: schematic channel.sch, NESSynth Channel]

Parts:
C2, C3: 100n; C_0805_HandSoldering
C4, C5: 18p; C_0805_HandSoldering
D1: LED; LED_0805
P1: NESSYNTH_SOCK; Pin_Header_Straight_2x08
P3: CONN_01X06; Pin_Header_Straight_1x06
P4: CONN_01X04; Pin_Header_Straight_1x04
R1, R2, R3, R4, R5, R7, R8, R10, R11, R12, R13: 1k; R_0805_HandSoldering
R6: 470; R_0805_HandSoldering
RV1: 10k; Potentiometer_Bourns_3386P
U1: ATMEGA88-A; TQFP-32_7x7mm_Pitch0.8mm
Y1: 14.31818 MHz; Crystal_HC49-U_Vertical

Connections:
/AUDIO_OUT: P1.1 (AUDIO_OUT), RV1.2
/BUS0: P1.6 (BUS0), U1.30 ((PCINT16/RXD)PD0)
/BUS1: P1.7 (BUS1), U1.31 ((PCINT17/TXD)PD1)
/BUS2: P1.8 (BUS2), U1.32 ((PCINT18/INT0)PD2)
/BUS3: P1.9 (BUS3), U1.1 ((PCINT19/OC2B/INT1)PD3)
/BUS4: P1.10 (BUS4), U1.2 ((PCINT20/XCK/T0)PD4)
/BUS5: P1.11 (BUS5), U1.9 ((PCINT21/OC0B/T1)PD5)
/BUS6: P1.13 (BUS6), U1.10 ((PCINT22/OC0A/AIN0)PD6)
/BUS7: P1.16 (BUS7), U1.11 ((PCINT23/AIN1)PD7)
/CONF0: P4.4, U1.13 ((PCINT1/OC1A)PB1)
/CONF1: P4.2, U1.14 ((PCINT2/OC1B/~SS~)PB2)
/DAC0: R1.1, U1.23 ((PCINT8/ADC0)PC0)
/DAC1: R5.1, U1.24 ((PCINT9/ADC1)PC1)
/DAC2: R10.1, U1.25 ((PCINT10/ADC2)PC2)
/DAC3: R13.1, U1.26 ((PCINT11/ADC3)PC3)
/DATA_CLK: P1.15 (DATA_CLK), U1.12 ((PCINT0/CLKO/ICP1)PB0)
/FRAME_CLK: P1.4 (FRAME_CLK), U1.28 ((PCINT13/SCL/ADC5)PC5)
/MISO: P3.5, U1.16 ((PCINT4/MISO)PB4)
/MOSI: P3.6, U1.15 ((PCINT3/OC2/MOSI)PB3)
/RESET: P1.5 (RESET), P3.3, U1.29 ((PCINT14/~RESET~)PC6)
/SCK: P3.4, U1.17 ((PCINT5/SCK)PB5)
/XTAL1: C4.2, U1.7 ((PCINT6/XTAL1/TOSC1)PB6), Y1.1
/XTAL2: C5.2, U1.8 ((PCINT7/XTAL2/TOSC2)PB7), Y1.2
GND: C2.2, C3.2, C4.1, C5.1, P1.14 (GND), P3.2, P4.1, P4.3, R6.2, U1.3 (GND), U1.5 (GND), U1.21 (GND)
GNDA: P1.2 (AGND), P1.3 (AGND), R2.2, RV1.1
unnamed: D1.1 (K), R6.1
unnamed: D1.2 (A), U1.27 ((PCINT12/SDA/ADC4)PC4)
unnamed: R1.2, R2.1, R3.2, R4.2
unnamed: R3.1, R4.1, R5.2, R7.2, R8.2
unnamed: R7.1, R8.1, R10.2, R11.2, R12.2
unnamed: R11.1, R12.1, R13.2, RV1.3
VCC: C2.1, C3.1, P1.12 (VCC), P3.1, U1.4 (VCC), U1.6 (VCC), U1.18 (AVCC)
